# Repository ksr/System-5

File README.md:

# System-5 — a PCB-based 1802 ELF

System-5 is a printed-circuit-board 1802 computer built in 2004–2005 to run
Mike Riley's **ELF/OS**. It replaced the wire-wrapped System-4 (1979–1982) one
card at a time while keeping the System-4 30-pin bus, so old wire-wrap cards and
new PCB cards could be mixed. All the 2005 boards were designed in **Eagle 4.x**;
the boards of 2026 are **KiCad** designs.

Original write-up: the 2005 1802 website, no longer online; a copy is in `docs/website-2005/`.

The project's website is <https://system5.cottageworker.com>. This repository is public as
<https://github.com/ksr/System-5>, a copy made from Ken's working repository (`tools/public/README.md`).

## The system

| Card | Folder | Summary |
|---|---|---|
| Bus | `hardware/bus` | The 30-pin bus kept from System-4: Rev A 1982, Rev B Dec 2005 (dropped ±12V, added N1/N2); pinout in `hardware/board-notes/BoardNotes.txt`. **In the machine: the 2009 PCB backplane**, six 36-pin slots, no regulator, no pull-ups (System-4's backplane was Vero board). **Rev D** (S5BUS-D, 2026, `kicad/rev-d/`): eight 36-pin slots, power switch, fuse, pull-ups and pull-downs. Designed, not ordered. |
| CPU | `hardware/cpu` | CDP1802, clock, CM1232 power-on reset/auto-run, mode control (run/load/wait/reset), 4K EPROM, VMA reset-address remap, EF jumpers, aux connectors for the front panel and 1861 card. **In the machine: Rev A** (Jan 2005, reworked). Rev B/C are unbuilt fixes; `eagle/cpu1-prototype` = first unrouted cut with the 1861 on board. **Rev D** (2026, `kicad/rev-d/`): a new CPU card for the 36-pin bus, 2 MHz or an external clock, RESET/RUN switch, a flag that lets a loaded program run from RAM after a reset, with a RAM LED to show it (2026-11-21). Designed, not ordered. |
| Memory | `hardware/memory` | 2× 62256 RAM + 2× 27256 EPROM, every 4K block jumper-enabled. **In the machine: Rev E** (MEM3-E, `kicad/rev-e/`; JLCPCB, 4 layers, built 2026-10-31): the 2005 Rev C circuit with three fixes. Before it: Rev A (2004, the first card built) → B (2005; reworked, in the machine until 2026) → C, and a 2014 `rev-c-mill` variant for PCB milling. Rev D (2026) is scrap. `mem1`/`mem2` are earlier 6116-based designs. |
| IO: 1861 video + keyboard | `hardware/io-1861-keyboard` | CDP1861 video, CDP1852 input port, I/O decode (from Mike Riley's ELF). PS/2 keyboard → **PAK-VI** (AWC Electronics PS/2-to-ASCII) → **PIC16F84** (serial→parallel, `pic-ps2-firmware/keyboard.c`) → 1852. **In the machine: Rev A** (Jan 2005), for the keyboard; the 1861 has never been tested. |
| 6845 video | `hardware/video-6845` | 6845 alphanumeric video card based on **BYTE, May 1979**. Composite + Electrohome drive outputs. Rev A Feb 2005 (the first working card, later stripped; `eagle/rev-a/`). **In the machine: Rev B** (lower case, simplified clocking, Apr 2005): the 2005 Eagle source in `eagle/rev-b/` and the KiCad order master in `kicad/rev-b/`. **Rev B-Clean** (2026, `kicad/rev-b-clean/`): Rev B's circuit and copper without the DE-9 (composite only) and with the 6845's light-pen input tied to ground, every part drawn and the silkscreen redone. Designed, not ordered. **Rev B-Clean-Keyboard** (2026, `kicad/rev-b-clean-keyboard/`): Rev B-Clean with a PS/2 keyboard on the card (VIDEO-G TEXT's keyboard section: the key at 7802, the status at 7804), the 36-pin bus connector, and the video and keyboard jacks together at the front edge; it runs the VIDEO-G HBIOS. Designed, not ordered. |
| CF disk (IDE) | `hardware/ide-cf` | Mike Riley's 8-bit IDE interface plus port-select jumpers; used with a CF-to-IDE adapter and a 16MB CF card. **In the machine: Rev A** (Feb 2005). |
| Breadboard proto | `hardware/proto-breadboard` | Solderless-breadboard prototyping card. Drawn in 2005, never made. |
| Bus driver | `hardware/bus-driver` | New, 2026: Arduino Nano and 2× MCP23017 on the bus, a test card after the YACC1 bus tester. It runs bus cycles in place of the CPU, or steps and traces the CPU. **Rev B** (BUSDRV-B, `kicad/rev-b/`; JLCPCB, 2 layers) is built and working since 2026-10-30. Rev A is scrap: routed on 4 layers, ordered from a 2-layer zip. **Rev C** (BUSDRV-C, `kicad/rev-c/`, drawn 2026-11-18, not ordered): all 36 bus positions with a third MCP23017, LOAD mode by the clock, CLK OUT and probes on the Nano, a DEBUG header cabled to CPU Rev D's. The firmware has a **short finder** for either card since 2026-11-21: one bus line driven alone, every other watched (`python3 bringup.py shorts`, `software/busdrv/BRINGUP.md`); tried in the simulator only. |
| IO panel | `hardware/io-panel` | New, 2026: the front panel as a card on the 36-pin bus. 8 toggles, 8 LEDs, six TIL311 hex displays (the data byte and the bus address), Q LED, INPUT button, ELF-style RUN/LOAD, a real-time clock and, since 2026-11-20, a serial port (16C550, DE-9). Since 2026-11-22 a 50-pin header at its front edge for the front panel's ribbon (the card is 8.00 in long), and its DMA request put right: as first drawn it would have loaded every byte twice. Since 2026-11-23 its own RESET button, which boots the EPROM (the RUN/RESET toggle restarts what ran before), and the serial port's settings on the silkscreen. Since 2026-11-25 its DMA request and the toggles' drive start from a known state at power-up (D1, R5, R6; U23 a 74HCT03), and since 2026-11-26 its RESET button is at the far end of the front edge from INPUT. Rev A (`kicad/rev-a/`) designed, not ordered. No front panel was designed in 2005: the System-4 wire-wrap panel was used via the CPU card header. |
| Front panel | `hardware/front-panel` | New, 2026-11-22: a board that mounts as the front of a case, on a 50-way ribbon from the IO panel card. Six TIL311s (the bus address and the data byte), bit and status LEDs (PWR, Q, PAUSE, RESET, ROM, START FROM RAM), eight data toggles, RUN and LOAD, INPUT, and a RESET button that boots the EPROM (beside START FROM RAM since 2026-11-26, away from INPUT). Nothing goes to the CPU card: a boot reset is a state of the bus (`docs/manual/bus.md`). Rev A (`kicad/rev-a/`) designed, not ordered. |
| VIDEO-G | `hardware/video-g` | New, 2026: the next video card, two boards joined by a 40-pin ribbon. **TEXT**: 6845 text, 64 × 25 or 64 × 32, with a PS/2 keyboard. **GFX**: graphics, 512 × 200 or 512 × 256, with a PS/2 mouse. All memory-mapped in its own block, no I/O ports (2026-11-17). Version 1.0 (`kicad/`) designed, not ordered. |

The machine today (2026-11-14) is the 2009 backplane with CPU Rev A, memory Rev E, 6845 Rev B, IO Rev A and IDE Rev A. The five new boards (bus Rev D, CPU Rev D, the IO panel and the two VIDEO-G boards) pass the older check, `tools/preorder_check.py`, and none is ordered. Before an order each has to pass `pcb-check`, Ken's check for the boards of all his systems since 2026-11-06 (`hardware/BUILD-RULES.md`, section 2): all five have, as they are now: the bus Rev D on 2026-11-18, the other four on 2026-11-19, after their labels were moved out from under the bus connector (and VIDEO-G TEXT got the 36-pin connector); the IO panel again on 2026-11-20, with its serial port; CPU Rev D again on 2026-11-21, with its RAM LED. On 2026-11-22 CPU Rev D and the IO panel were changed and a sixth board, the front panel, was drawn (a boot reset on the bus; the IO panel's header and its DMA request): all three pass `pcb-check --tests` (last on 2026-11-23, at `26e17ea`: CPU Rev D and the front panel with no failures and no warnings, the IO panel with no failures and one warning, which Ken accepted that day: its DE-9 begins 65.6 mm from the front edge, where the check allows 60). They were drawn on the branch `front-panel` and are in `main` since 2026-11-23 (Ken: "merge everything"). Since then: VIDEO-G TEXT routed again with its 6845 write-only (2026-11-24; `pcb-check --tests` at `38fc4d0`, no failures, 0 warnings, GFX the same), the IO panel's power-up fix (2026-11-25), and both panels' RESET buttons moved away from INPUT (2026-11-26; `pcb-check --tests`: the front panel at `803c3a8`, no failures, 0 warnings; the IO panel at `6f4359d`, no failures, the accepted warning). None is ordered. `STATUS.md` has every board's state.

Board conventions (size 5.50" × 3.75", LED positions, labelling `KSR -- XXX#-A`,
CAM jobs) are in `hardware/board-notes/`.

Each board has an `eagle/<rev>/` tree (production gerbers in `fab/`) and, once converted, a `kicad/<rev>/` tree. Which boards were ordered: `hardware/FABRICATED.md`. Open work: `BACKLOG.md`. A summary of where everything stands (2026-11-14): `STATUS.md`.

Where both the Eagle working folder and the published website had a file with
the same name but different content, the website version is kept in a
`website-copy/` subfolder. Eagle's numbered backups (`*.b#1`, `*.s##`, …) are in
`eagle-backups/` subfolders.

## Firmware (Ken's)

- `firmware/hbios/` — **HBIOS**: 6845 video and keyboard drivers layered on Mike
  Riley's ELF/OS BIOS (changes marked `#define KSR`); boots into the BIOS's
  monitor, `minimon`, which is Mike's. `v1.0.6` is current, in the machine since 2026-11-15 (v1.0.4 plus the commands
  Ken added to that monitor, `H`, `B`, `D` and `Q1` / `Q0`, and the disk calls
  always in LBA mode, which Elf/OS v5 needs; built by its `build.py`); `v1.0.5`, `v1.0.4`, `v0.9` and `old/` are
  earlier builds. `v1.0.7` (2026-11-17, burned that day, not yet in the machine) adds `@F1E0`: the code of each key pressed, as `0x31`, on the
  bottom line of the screen, until Reset. `v1.0.8` (2026-11-18, emulator only) adds a driver for the IO panel's real-time
  clock (a DS12885 on ports 6/7) behind `f_gettod` / `f_settod`, and `f_getdev` bit 4. v1.0.4 builds with `rcasm` + `srec_cat` into a ROM
  at `0xF000`. `video-g/` is a build for the VIDEO-G card (everything
  memory-mapped: the 6845 at 7800/7801, the key at 7802; 64 x 25, a faster scroll; for the emulator, not burned).
  Mike Riley's BIOS comes under his notice (`firmware/hbios/NOTICE.md`: free to use and share with the notice kept,
  not for commercial use without his permission).
- `firmware/rom-tests/` — test ROM (`sec2`).
- `firmware/char-rom-fonts/` — 2513 character-generator ROM images and C tools
  to build/view font EPROMs for the 6845 card.

## Software (Ken's host tools)

- `software/s5emu/` — System-5 emulator and debugger (terminal + browser; in a browser tab on a Mac or in a GitHub Codespace: `software/s5emu/CODESPACE.md`, `.devcontainer/`): runs the real HBIOS ROM and boots ELF/OS from a disk image; 1861, IDE/CF, 6845, keyboard, memory jumpers, bus-driver link; `--video g` models the VIDEO-G card.

- `software/gbasic/` — **GBASIC**, an integer BASIC for ELF/OS with VIDEO-G graphics (1802 assembly, 2026-11-01): the source, the built program, its language reference (`README.md`) and tests in the emulator.

- `tools/render_populated.py` — a KiCad render of a board with its parts drawn in, for the website's pictures (the board file is only read)
- `tools/asm1802.py` — a Python 1802 assembler (rcasm syntax, short-branch page check, relaxing jumps, macros); builds GBASIC and the VIDEO-G HBIOS.

- `software/busdrv/` — `s5busdrv.py`, the host tool for the bus driver card (peek/poke/dump, hex load with verify, memtest, I/O, bus watch); firmware in `embedded/bus-driver/`.

- `software/elfos-v5/` — System-5 programs for Mike Riley's Elf/OS v5 (`cls`) and `v5card.py`, which reads and
  changes a v5 card image (`ls`, `get`, `put`, `add`).

## Kept private (third-party)

Other people's work that System-5 is built with, and that carries no permission to publish it, is not in this
repository. Since 2026-11-15 it is in Ken's private repository `private-resources` (`github.com/ksr/private-resources`),
which sits beside this one, so the paths below are written `../private-resources/elf/...`; each keeps the path it had
here.

- `reference/mike-riley/` — **ELF/OS** (kernel 135, utilities and languages,
  0.2.6 release; Elf/OS v5 and its System-5 card image), **rcasm** 2007 source, **EDTASM**, MicroElf/PicoElf boards
  and a mirror of elf-emulation.com.
- `reference/elf2000-spare-time-gizmos/` — **ELF2000** (Spare Time Gizmos /
  Bob Armstrong): manuals, EELF, ELF-Disk, STG1861, ROM v60/v87 images (with
  Ken's EPROM-split Makefiles), ElfOS-2K 0.2.8. Not part of System-5.
- `reference/tiny-basic/` — Lee Hart/TMSI 1802 Tiny BASIC; RCA Tiny BASIC (Herb Johnson).
- `reference/tools/` — A18 assembler, TASM 3.1, 1806 disassembler, srecord
  source tarballs (1.20/1.23/1.27), Macro Assembler AS manual, LCD font tool.
- `reference/datasheets/` — CDP1802 datasheet, RCA MPM-201A 1802 User Manual (1976), EPROM databook.
- `firmware/elfos-install-rom/` — the ELF/OS install image for the memory card's EPROM, and the read of the one in
  MEM3-E's IC5 (`hardware/memory/eagle/rev-b/bringup/*.bin`).
- `firmware/system4-tiny-basic-rom/` — the Tiny BASIC EPROM pulled from the System-4 wire-wrap machine, and its
  disassembly.
- `software/disktool/` — Mike Riley's 2005 disktool, which builds and writes ELF/OS disks (with `kernel.bin`).
- `software/rcasm-mac-build/` — rcasm source patched in 2017 to build on macOS (with a Mac x86_64 binary).

Without them the emulator still runs HBIOS (whose BIOS part Mike Riley allows to be shared, above), but has no ELF/OS
disk to boot, and the tests that need one are skipped.

## Licence

Ken's designs and documents are CC BY 4.0, his software MIT; HBIOS's BIOS part, the 2513 fonts and some library parts
are other people's: [`LICENSE.md`](LICENSE.md).

## Docs

- `docs/website-2005/` — "Ken's 1802 World" site (System-1, System-4, System-5,
  stand-alone projects, photos). Files that are also elsewhere in this repo
  (schematics, BIOS source, tool tarballs) were removed here (the list is
  `docs/.removed-dups.txt`, kept with Ken's working notes).
- `docs/website-older/` — earlier versions of the same site.

The visitor counter the Yahoo host added to 33 of the old pages was taken out on 2026-11-15; nothing else in them was
changed.

## Other projects

1802 work that is not System-5 (the Netronics ELF II recreation, the 2020 COSMAC ELF PCB, the ELF2000/PicoElf
ROMs, the ET-3400 EPROM reads and general 1802 documentation) is in a separate private repository since 2026-10-26,
split out of this one with its history.

## Provenance

Assembled 2026-10-04 from `~/Documents/Projects/elf-1`, `elf-2` and `1802`
(all left untouched). `elf-1` was largely a subset of `elf-2`; exact duplicates were
collapsed to one copy. Not carried over: FrontPage `_vti_*` metadata, vim swap
files, `.o` objects, extracted srecord build trees (source tarballs kept), and
2005-era Linux i386 binaries that have source alongside. Duplicate include
files inside individual ELF/OS program folders were left in place because each
program's build expects them.

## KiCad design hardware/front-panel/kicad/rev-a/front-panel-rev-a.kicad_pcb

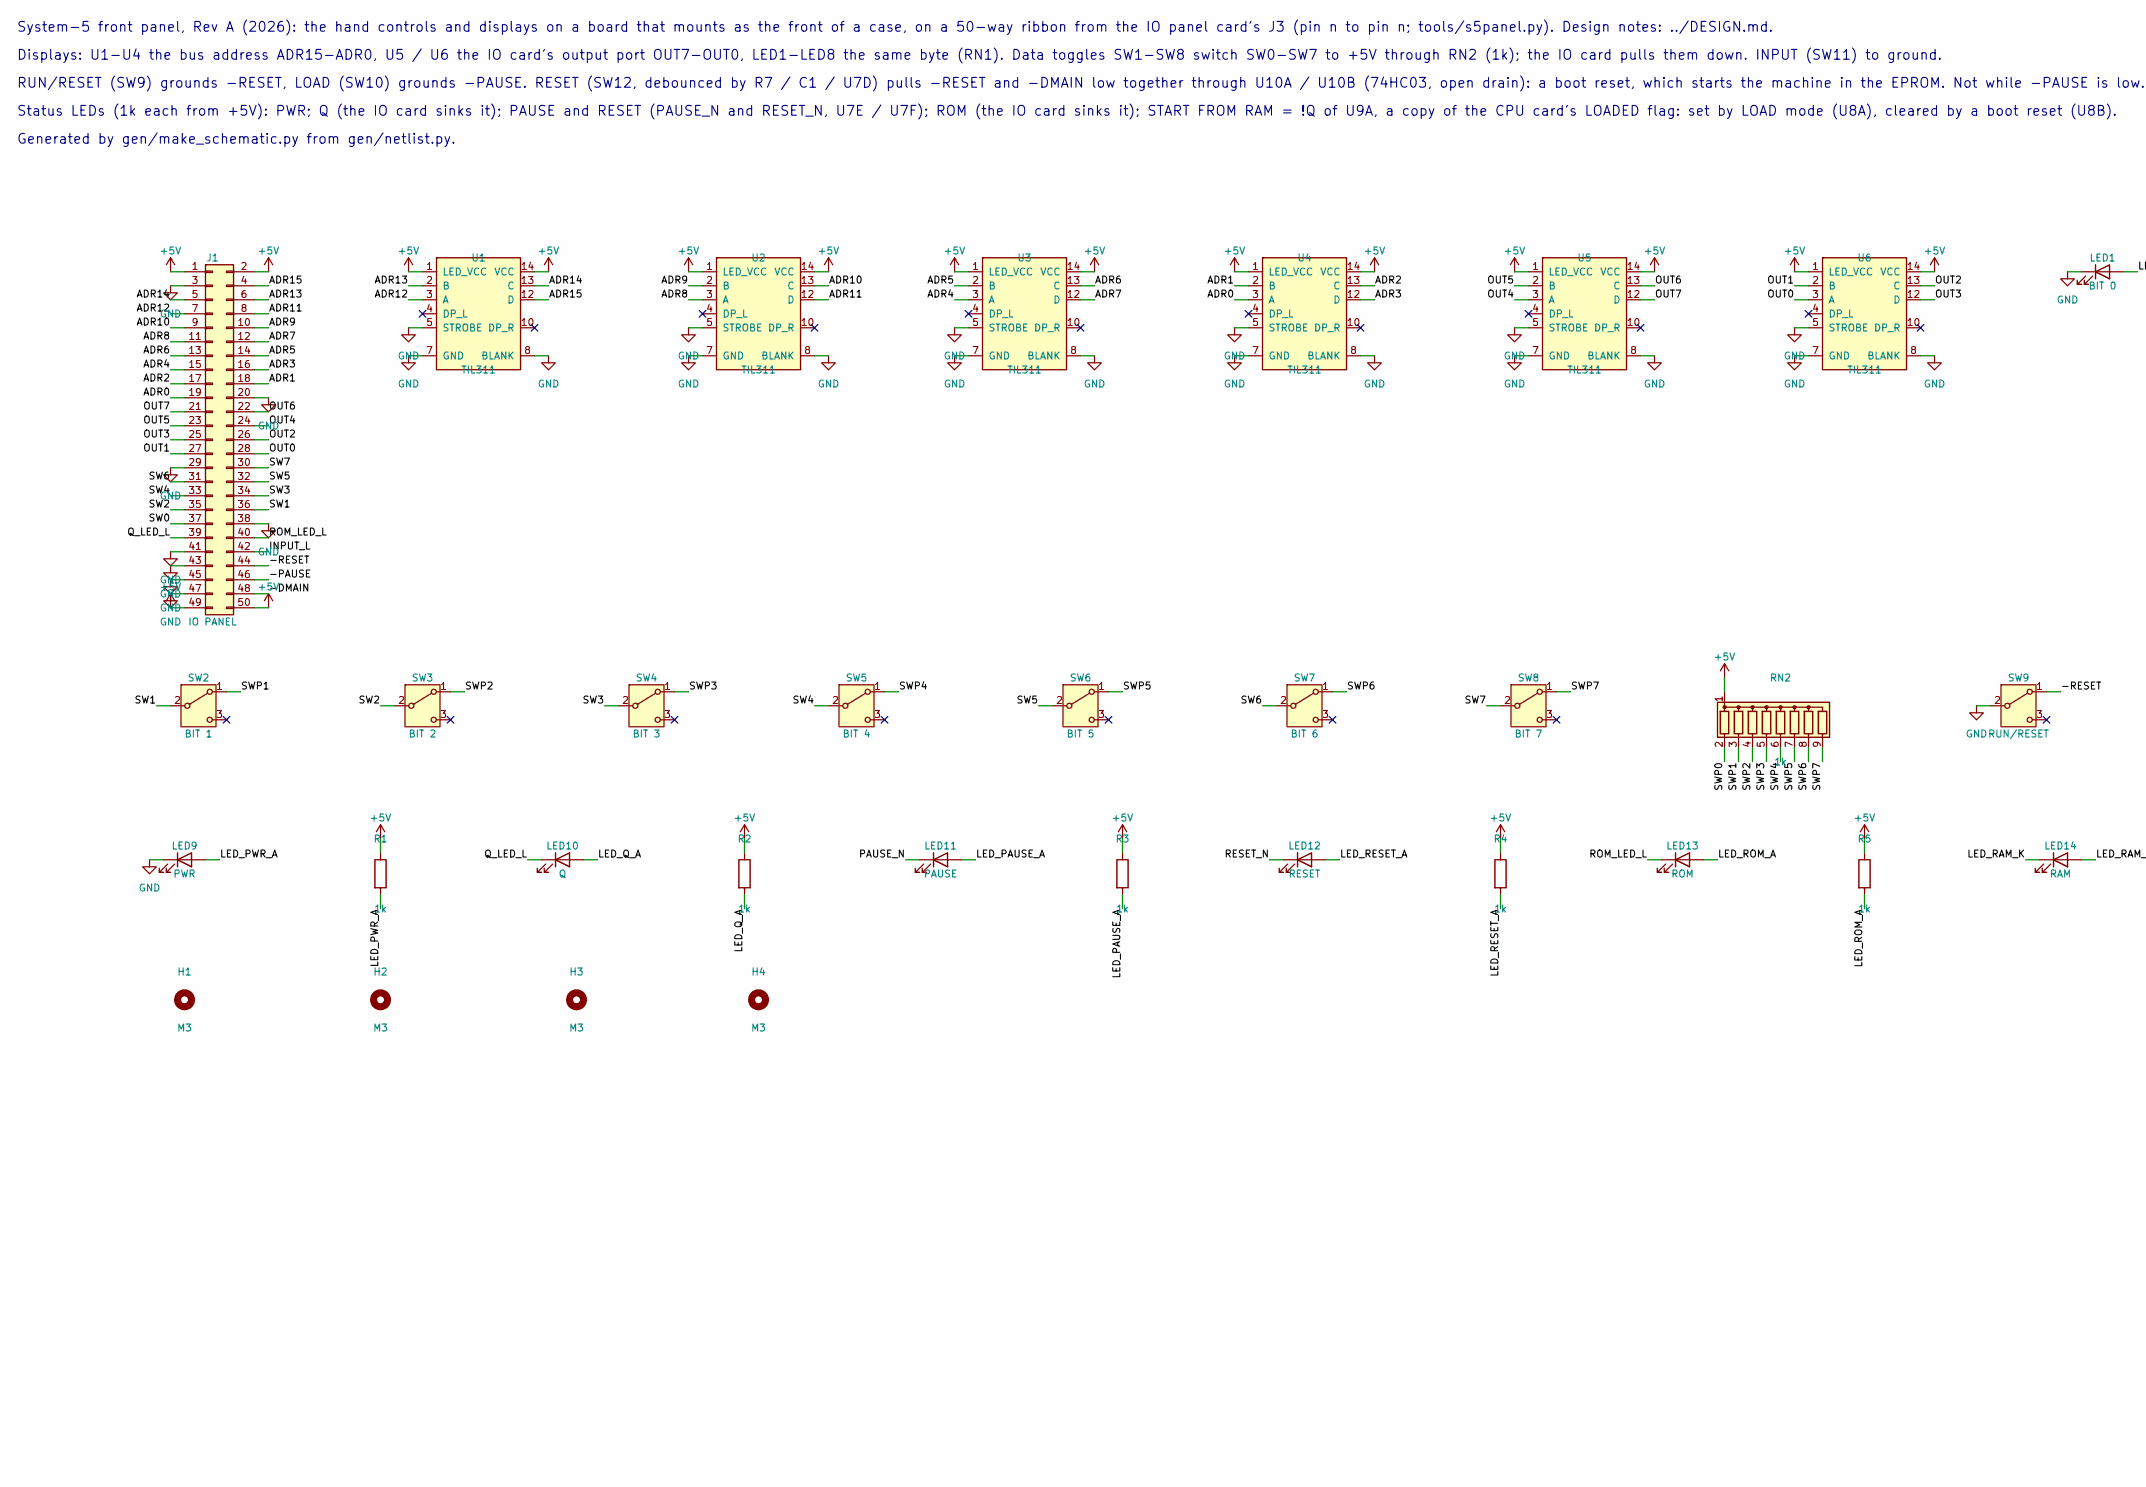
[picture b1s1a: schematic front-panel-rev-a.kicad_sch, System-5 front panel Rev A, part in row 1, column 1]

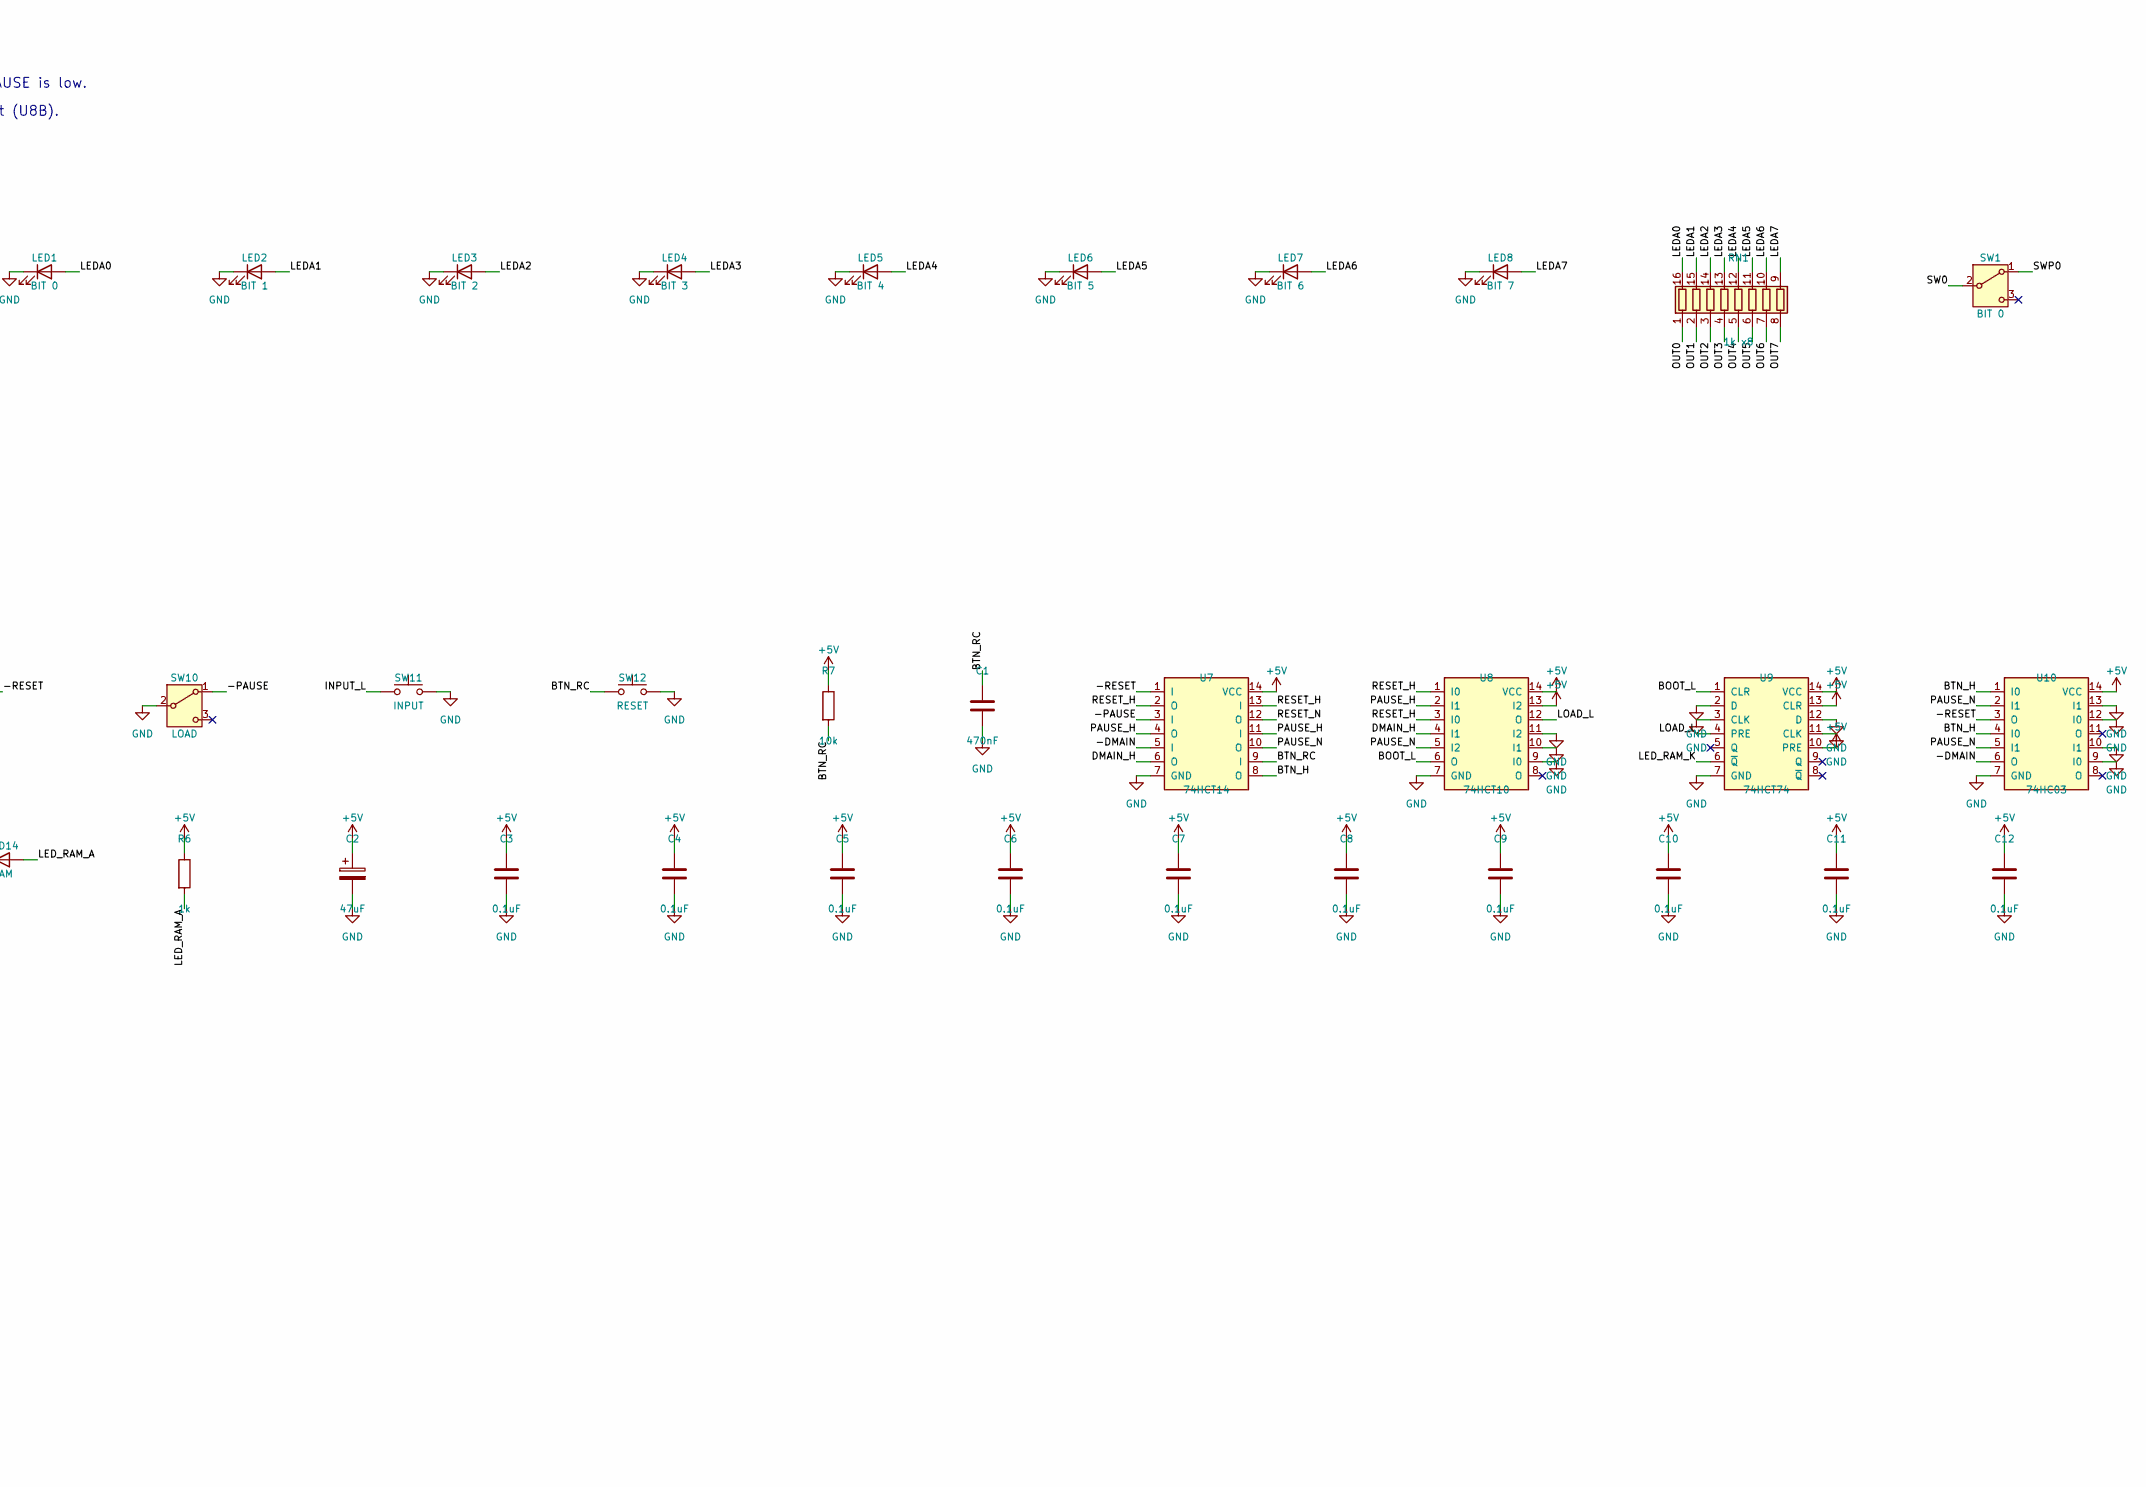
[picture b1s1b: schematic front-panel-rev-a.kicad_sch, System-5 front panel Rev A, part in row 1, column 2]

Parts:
C1: 470nF; C_Disc_D5.0mm_W2.5mm_P2.50mm
C2: 47uF; CP_Radial_D6.3mm_P2.50mm
C3, C4, C5, C6, C7, C8, C9, C10, C11, C12: 0.1uF; C025-050X050
H1, H2, H3, H4: M3; MountingHole_3.2mm_M3
J1: IO PANEL; IDC-Header_2x25_P2.54mm_Vertical
LED1: BIT 0; LED_D3.0mm
LED2: BIT 1; LED_D3.0mm
LED3: BIT 2; LED_D3.0mm
LED4: BIT 3; LED_D3.0mm
LED5: BIT 4; LED_D3.0mm
LED6: BIT 5; LED_D3.0mm
LED7: BIT 6; LED_D3.0mm
LED8: BIT 7; LED_D3.0mm
LED9: PWR; LED_D3.0mm
LED10: Q; LED_D3.0mm
LED11: PAUSE; LED_D3.0mm
LED12: RESET; LED_D3.0mm
LED13: ROM; LED_D3.0mm
LED14: RAM; LED_D3.0mm
R1, R2, R3, R4, R5, R6: 1k; R_Axial_DIN0207_L6.3mm_D2.5mm_P7.62mm_Horizontal
R7: 10k; R_Axial_DIN0207_L6.3mm_D2.5mm_P7.62mm_Horizontal
RN1: 1k x8; DIP-16_W7.62mm
RN2: 1k; R_Array_SIP9
SW1: BIT 0; M9040P
SW2: BIT 1; M9040P
SW3: BIT 2; M9040P
SW4: BIT 3; M9040P
SW5: BIT 4; M9040P
SW6: BIT 5; M9040P
SW7: BIT 6; M9040P
SW8: BIT 7; M9040P
SW9: RUN/RESET; M9040P
SW10: LOAD; M9040P
SW11: INPUT; SW_PUSH_6mm
SW12: RESET; SW_PUSH_6mm
U1, U2, U3, U4, U5, U6: TIL311; HTIL311A
U7: 74HCT14; DIP-14_W7.62mm
U8: 74HCT10; DIP-14_W7.62mm
U9: 74HCT74; DIP-14_W7.62mm
U10: 74HC03; DIP-14_W7.62mm

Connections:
+5V: C2.1, C3.1, C4.1, C5.1, C6.1, C7.1, C8.1, C9.1, C10.1, C11.1, C12.1, J1.1, J1.2, J1.49, J1.50, R1.1, R2.1, R3.1, R4.1, R5.1, R6.1, R7.1, RN2.1 (common), U1.1 (LED_VCC), U1.14 (VCC), U2.1 (LED_VCC), U2.14 (VCC), U3.1 (LED_VCC), U3.14 (VCC), U4.1 (LED_VCC), U4.14 (VCC), U5.1 (LED_VCC), U5.14 (VCC), U6.1 (LED_VCC), U6.14 (VCC), U7.14 (VCC), U8.13 (I2), U8.14 (VCC), U9.10 (PRE), U9.13 (CLR), U9.14 (VCC), U10.14 (VCC)
/-DMAIN: J1.48, U7.5 (I), U10.6 (O)
/-PAUSE: J1.46, SW10.1 (A), U7.3 (I)
/-RESET: J1.44, SW9.1 (A), U7.1 (I), U10.3 (O)
/ADR0: J1.19, U4.3 (A)
/ADR1: J1.18, U4.2 (B)
/ADR2: J1.17, U4.13 (C)
/ADR3: J1.16, U4.12 (D)
/ADR4: J1.15, U3.3 (A)
/ADR5: J1.14, U3.2 (B)
/ADR6: J1.13, U3.13 (C)
/ADR7: J1.12, U3.12 (D)
/ADR8: J1.11, U2.3 (A)
/ADR9: J1.10, U2.2 (B)
/ADR10: J1.9, U2.13 (C)
/ADR11: J1.8, U2.12 (D)
/ADR12: J1.7, U1.3 (A)
/ADR13: J1.6, U1.2 (B)
/ADR14: J1.5, U1.13 (C)
/ADR15: J1.4, U1.12 (D)
/BOOT_L: U8.6 (O), U9.1 (CLR)
/BTN_H: U7.8 (O), U10.1 (I0), U10.4 (I0)
/BTN_RC: C1.1, R7.2, SW12.1, U7.9 (I)
/DMAIN_H: U7.6 (O), U8.4 (I1)
/INPUT_L: J1.42, SW11.1
/LEDA0: LED1.2 (A), RN1.16 (R1.2)
/LEDA1: LED2.2 (A), RN1.15 (R2.2)
/LEDA2: LED3.2 (A), RN1.14 (R3.2)
/LEDA3: LED4.2 (A), RN1.13 (R4.2)
/LEDA4: LED5.2 (A), RN1.12 (R5.2)
/LEDA5: LED6.2 (A), RN1.11 (R6.2)
/LEDA6: LED7.2 (A), RN1.10 (R7.2)
/LEDA7: LED8.2 (A), RN1.9 (R8.2)
/LED_PAUSE_A: LED11.2 (A), R3.2
/LED_PWR_A: LED9.2 (A), R1.2
/LED_Q_A: LED10.2 (A), R2.2
/LED_RAM_A: LED14.2 (A), R6.2
/LED_RAM_K: LED14.1 (K), U9.6 (~Q)
/LED_RESET_A: LED12.2 (A), R4.2
/LED_ROM_A: LED13.2 (A), R5.2
/LOAD_L: U8.12 (O), U9.4 (PRE)
/OUT0: J1.28, RN1.1 (R1.1), U6.3 (A)
/OUT1: J1.27, RN1.2 (R2.1), U6.2 (B)
/OUT2: J1.26, RN1.3 (R3.1), U6.13 (C)
/OUT3: J1.25, RN1.4 (R4.1), U6.12 (D)
/OUT4: J1.24, RN1.5 (R5.1), U5.3 (A)
/OUT5: J1.23, RN1.6 (R6.1), U5.2 (B)
/OUT6: J1.22, RN1.7 (R7.1), U5.13 (C)
/OUT7: J1.21, RN1.8 (R8.1), U5.12 (D)
/PAUSE_H: U7.4 (O), U7.11 (I), U8.2 (I1)
/PAUSE_N: LED11.1 (K), U7.10 (O), U8.5 (I2), U10.2 (I1), U10.5 (I1)
/Q_LED_L: J1.39, LED10.1 (K)
/RESET_H: U7.2 (O), U7.13 (I), U8.1 (I0), U8.3 (I0)
/RESET_N: LED12.1 (K), U7.12 (O)
/ROM_LED_L: J1.40, LED13.1 (K)
/SW0: J1.37, SW1.2 (B)
/SW1: J1.36, SW2.2 (B)
/SW2: J1.35, SW3.2 (B)
/SW3: J1.34, SW4.2 (B)
/SW4: J1.33, SW5.2 (B)
/SW5: J1.32, SW6.2 (B)
/SW6: J1.31, SW7.2 (B)
/SW7: J1.30, SW8.2 (B)
/SWP0: RN2.2 (R1), SW1.1 (A)
/SWP1: RN2.3 (R2), SW2.1 (A)
/SWP2: RN2.4 (R3), SW3.1 (A)
/SWP3: RN2.5 (R4), SW4.1 (A)
/SWP4: RN2.6 (R5), SW5.1 (A)
/SWP5: RN2.7 (R6), SW6.1 (A)
/SWP6: RN2.8 (R7), SW7.1 (A)
/SWP7: RN2.9 (R8), SW8.1 (A)
GND: C1.2, C2.2, C3.2, C4.2, C5.2, C6.2, C7.2, C8.2, C9.2, C10.2, C11.2, C12.2, J1.3, J1.20, J1.29, J1.38, J1.41, J1.43, J1.45, J1.47, LED1.1 (K), LED2.1 (K), LED3.1 (K), LED4.1 (K), LED5.1 (K), LED6.1 (K), LED7.1 (K), LED8.1 (K), LED9.1 (K), SW9.2 (B), SW10.2 (B), SW11.2, SW12.2, U1.5 (STROBE), U1.7 (GND), U1.8 (BLANK), U2.5 (STROBE), U2.7 (GND), U2.8 (BLANK), U3.5 (STROBE), U3.7 (GND), U3.8 (BLANK), U4.5 (STROBE), U4.7 (GND), U4.8 (BLANK), U5.5 (STROBE), U5.7 (GND), U5.8 (BLANK), U6.5 (STROBE), U6.7 (GND), U6.8 (BLANK), U7.7 (GND), U8.7 (GND), U8.9 (I0), U8.10 (I1), U8.11 (I2), U9.2 (D), U9.3 (CLK), U9.7 (GND), U9.11 (CLK), U9.12 (D), U10.7 (GND), U10.9 (I0), U10.10 (I1), U10.12 (I0), U10.13 (I1)

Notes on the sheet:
System-5 front panel, Rev A (2026): the hand controls and displays on a board that mounts as the front of a case, on a 50-way ribbon from the IO panel card's J3 (pin n to pin n; tools/s5panel.py). Design notes: ../DESIGN.md.
Displays: U1-U4 the bus address ADR15-ADR0, U5 / U6 the IO card's output port OUT7-OUT0, LED1-LED8 the same byte (RN1). Data toggles SW1-SW8 switch SW0-SW7 to +5V through RN2 (1k); the IO card pulls them down. INPUT (SW11) to ground.
RUN/RESET (SW9) grounds -RESET, LOAD (SW10) grounds -PAUSE. RESET (SW12, debounced by R7 / C1 / U7D) pulls -RESET and -DMAIN low together through U10A / U10B (74HC03, open drain): a boot reset, which starts the machine in the EPROM. Not while -PAUSE is low.
Status LEDs (1k each from +5V): PWR; Q (the IO card sinks it); PAUSE and RESET (PAUSE_N and RESET_N, U7E / U7F); ROM (the IO card sinks it); START FROM RAM = !Q of U9A, a copy of the CPU card's LOADED flag: set by LOAD mode (U8A), cleared by a boot reset (U8B).
Generated by gen/make_schematic.py from gen/netlist.py.

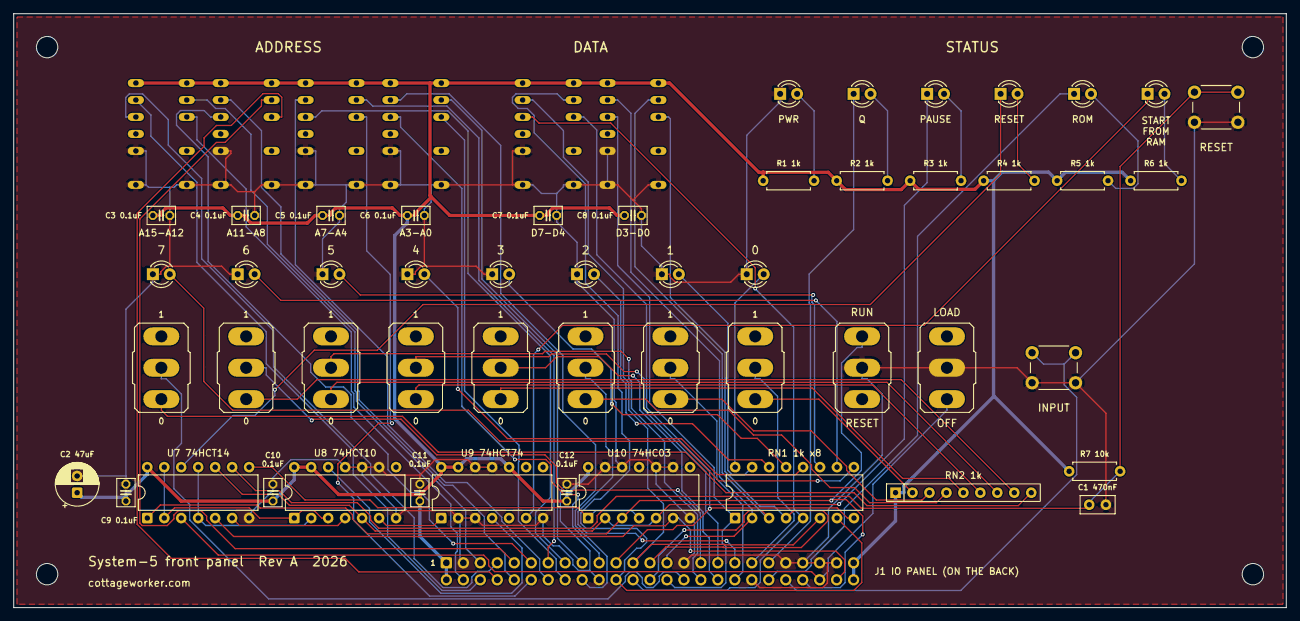
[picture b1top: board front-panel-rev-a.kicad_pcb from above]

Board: 2 copper layers, 190.5 x 88.9 mm, 62 parts (1 on the bottom side), 72 nets.
